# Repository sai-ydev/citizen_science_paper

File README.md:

# Purple Daisy RP2350A STEAM Platform #

This is the repository for the Purple Daisy Platform based on the [Raspberry Pi RP2350A Microcontroller](https://www.raspberrypi.com/products/rp2350/). This is an open-source platform to conduct citizen science experiments using the Raspberry Pi RP2350A microcontroller. 

The board looks something like shown in the image below:

The components of the board are highlighted in the image below. They are as follows:

1. Raspberry PI RP2350A microcontroller
2. RGB seven segment display - 4 characters
3. MicroSD card slot
4. Buzzer
5. WiFi Module
6. USB-C port
7. Soil Moisture sensor
8. AS3935 Lightning Sensor
9. pH Sensor + Conditioning Circuit
10. Liquid Temperature sensor
11. QwiiC I2C Sensor port to connect additional sensors
12. Real Time Clock for Calendar Keeping
13. Debug Port for debugging
14. BME690 Air Quality Sensor
15. ENS210 Temperature Humidity Sensor

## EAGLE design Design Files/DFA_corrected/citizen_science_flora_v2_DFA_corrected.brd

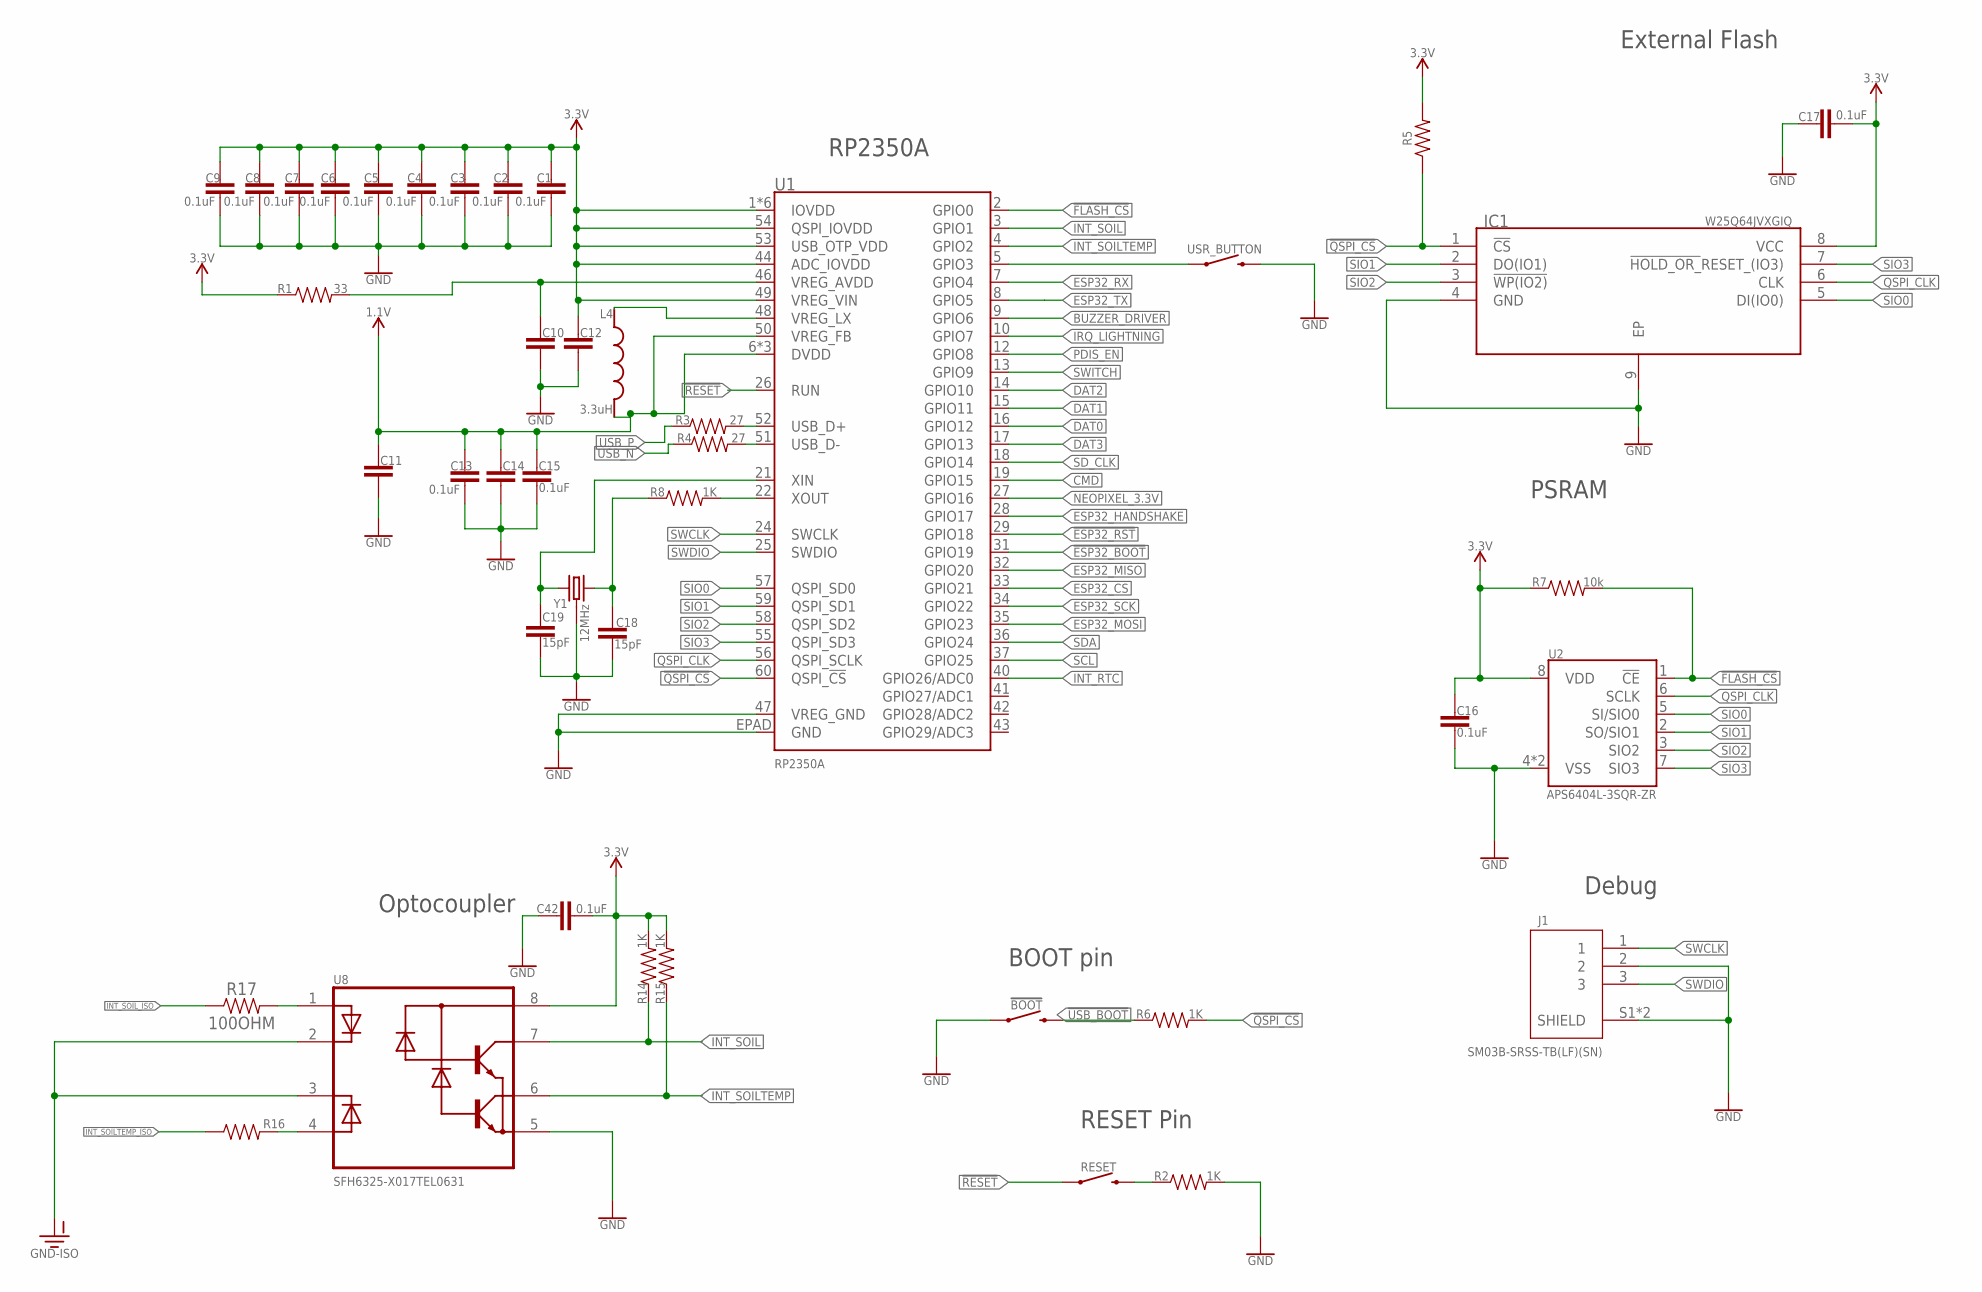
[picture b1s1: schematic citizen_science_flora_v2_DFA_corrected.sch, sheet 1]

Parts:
!BOOT: MOMENTARY-SWITCH-SPST-SMD-4.6X2.8MM; TACTILE_SWITCH_SMD_4.6X2.8MM
C1, C2, C3, C4, C5, C6, C7, C8, C9, C13, C15, C16, C17, C42: 0.1uF; 0402
C10, C11, C12, C14: 4.7UF0402; 0402
C18, C19: 15pF; 0402
IC1: W25Q64JVXGIQ; SON80P400X400X50-9N
J1: SM03B-SRSS-TB(LF)(SN); JST_SM03B-SRSS-TB(LF)(SN)
L4: 3.3uH; IND_LQH2MCN120K02L
R1: 33; 0402
R2, R6, R8, R14, R15: 1K; 0402
R3, R4: 27; 0402
R5: 0402
R7: 10k; 0402
R16, R17: 100OHM; 0402
RESET: MOMENTARY-SWITCH-SPST-SMD-4.6X2.8MM; TACTILE_SWITCH_SMD_4.6X2.8MM
U1: RP2350A
U2: APS6404L-3SQR-ZR
U8: SFH6325-X017TEL0631; SOIC127P599X175-8N
USR_BUTTON: MOMENTARY-SWITCH-SPST-SMD-4.6X2.8MM; TACTILE_SWITCH_SMD_4.6X2.8MM
Y1: 12MHz; CRYSTAL-SMD-3.2X2.5MM

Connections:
1.1V: C11.1, C13.1, C14.1, C15.1, L4.2, U1.6 (DVDD), U1.23 (DVDD), U1.39 (DVDD), U1.50 (VREG_FB)
3.3V: C1.1, C2.1, C3.1, C4.1, C5.1, C6.1, C7.1, C8.1, C9.1, C12.1, C16.1, C17.2, C42.2, IC1.8 (VCC), R1.1, R5.2, R7.1, R14.2, R15.2, U1.1 (IOVDD), U1.11 (IOVDD), U1.20 (IOVDD), U1.30 (IOVDD), U1.38 (IOVDD), U1.44 (ADC_IOVDD), U1.45 (IOVDD), U1.49 (VREG_VIN), U1.53 (USB_OTP_VDD), U1.54 (QSPI_IOVDD), U2.8 (VDD), U8.8 (C(VCC)); also elsewhere on the board
!ESP32_BOOT: U1.31 (GPIO19); also elsewhere on the board
!ESP32_RST: U1.29 (GPIO18); also elsewhere on the board
!FLASH_CS: R7.2, U1.2 (GPIO0), U2.1 (!CE!)
!QSPI_CS: IC1.1 (!CS), R5.1, R6.2, U1.60 (QSPI_!CS!)
!RESET: RESET.1, RESET.2 (1), U1.26 (RUN)
!USB_BOOT: !BOOT.3 (2), !BOOT.4 (2), R6.1
BUZZER_DRIVER: U1.9 (GPIO6); also elsewhere on the board
CMD: U1.19 (GPIO15); also elsewhere on the board
DAT0: U1.16 (GPIO12); also elsewhere on the board
DAT1: U1.15 (GPIO11); also elsewhere on the board
DAT2: U1.14 (GPIO10); also elsewhere on the board
DAT3: U1.17 (GPIO13); also elsewhere on the board
ESP32_CS: U1.33 (GPIO21); also elsewhere on the board
ESP32_HANDSHAKE: U1.28 (GPIO17); also elsewhere on the board
ESP32_MISO: U1.32 (GPIO20); also elsewhere on the board
ESP32_MOSI: U1.35 (GPIO23); also elsewhere on the board
ESP32_RX: U1.7 (GPIO4); also elsewhere on the board
ESP32_SCK: U1.34 (GPIO22); also elsewhere on the board
ESP32_TX: U1.8 (GPIO5); also elsewhere on the board
GND: !BOOT.1, !BOOT.2 (1), C1.2, C2.2, C3.2, C4.2, C5.2, C6.2, C7.2, C8.2, C9.2, C10.2, C11.2, C12.2, C13.2, C14.2, C15.2, C16.2, C17.1, C18.2, C19.2, C42.1, IC1.4 (GND), IC1.9 (EP), J1.2, J1.S1 (SHIELD), J1.S2 (SHIELD), R2.2, U1.47 (VREG_GND), U1.EPAD (GND), U2.4 (VSS), U2.9 (VSS), U8.5 (E(GND)), USR_BUTTON.3 (2), USR_BUTTON.4 (2), Y1.2 (GND), Y1.4 (GND); also elsewhere on the board
GND-ISO: U8.2 (C1), U8.3 (C2); also elsewhere on the board
INT_RTC: U1.40 (GPIO26/ADC0); also elsewhere on the board
INT_SOIL: R14.1, U1.3 (GPIO1), U8.7 (C1(VO1))
INT_SOILTEMP: R15.1, U1.4 (GPIO2), U8.6 (C2(VO2))
INT_SOILTEMP_ISO: R16.1; also elsewhere on the board
INT_SOIL_ISO: R17.1; also elsewhere on the board
IRQ_LIGHTNING: U1.10 (GPIO7); also elsewhere on the board
unnamed: C10.1, R1.2, U1.46 (VREG_AVDD)
unnamed: L4.1, U1.48 (VREG_LX)
unnamed: R2.1, RESET.3 (2), RESET.4 (2)
unnamed: C18.1, R8.1, Y1.3 (2)
unnamed: C19.1, U1.21 (XIN), Y1.1
unnamed: R8.2, U1.22 (XOUT)
unnamed: R16.2, U8.4 (A2)
unnamed: R17.2, U8.1 (A1)
unnamed: U1.5 (GPIO3), USR_BUTTON.1, USR_BUTTON.2 (1)
NEOPIXEL_3.3V: U1.27 (GPIO16); also elsewhere on the board
PDIS_EN: U1.12 (GPIO8); also elsewhere on the board
QSPI_CLK: IC1.6 (CLK), U1.56 (QSPI_SCLK), U2.6 (SCLK)
SCL: U1.37 (GPIO25); also elsewhere on the board
SDA: U1.36 (GPIO24); also elsewhere on the board
SD_CLK: U1.18 (GPIO14); also elsewhere on the board
SIO0: IC1.5 (DI(IO0)), U1.57 (QSPI_SD0), U2.5 (SI/SIO0)
SIO1: IC1.2 (DO(IO1)), U1.59 (QSPI_SD1), U2.2 (SO/SIO1)
SIO2: IC1.3 (!WP(IO2)), U1.58 (QSPI_SD2), U2.3 (SIO2)
SIO3: IC1.7 (!HOLD_OR_!RESET_(IO3)), U1.55 (QSPI_SD3), U2.7 (SIO3)
SWCLK: J1.1, U1.24 (SWCLK)
SWDIO: J1.3, U1.25 (SWDIO)
SWITCH: U1.13 (GPIO9); also elsewhere on the board
USBD_N: R4.2, U1.51 (USB_D-)
USBD_P: R3.2, U1.52 (USB_D+)
USB_N: R4.1; also elsewhere on the board
USB_P: R3.1; also elsewhere on the board

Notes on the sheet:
RP2350A
RESET Pin
External Flash
BOOT pin
PSRAM
Debug
Optocoupler

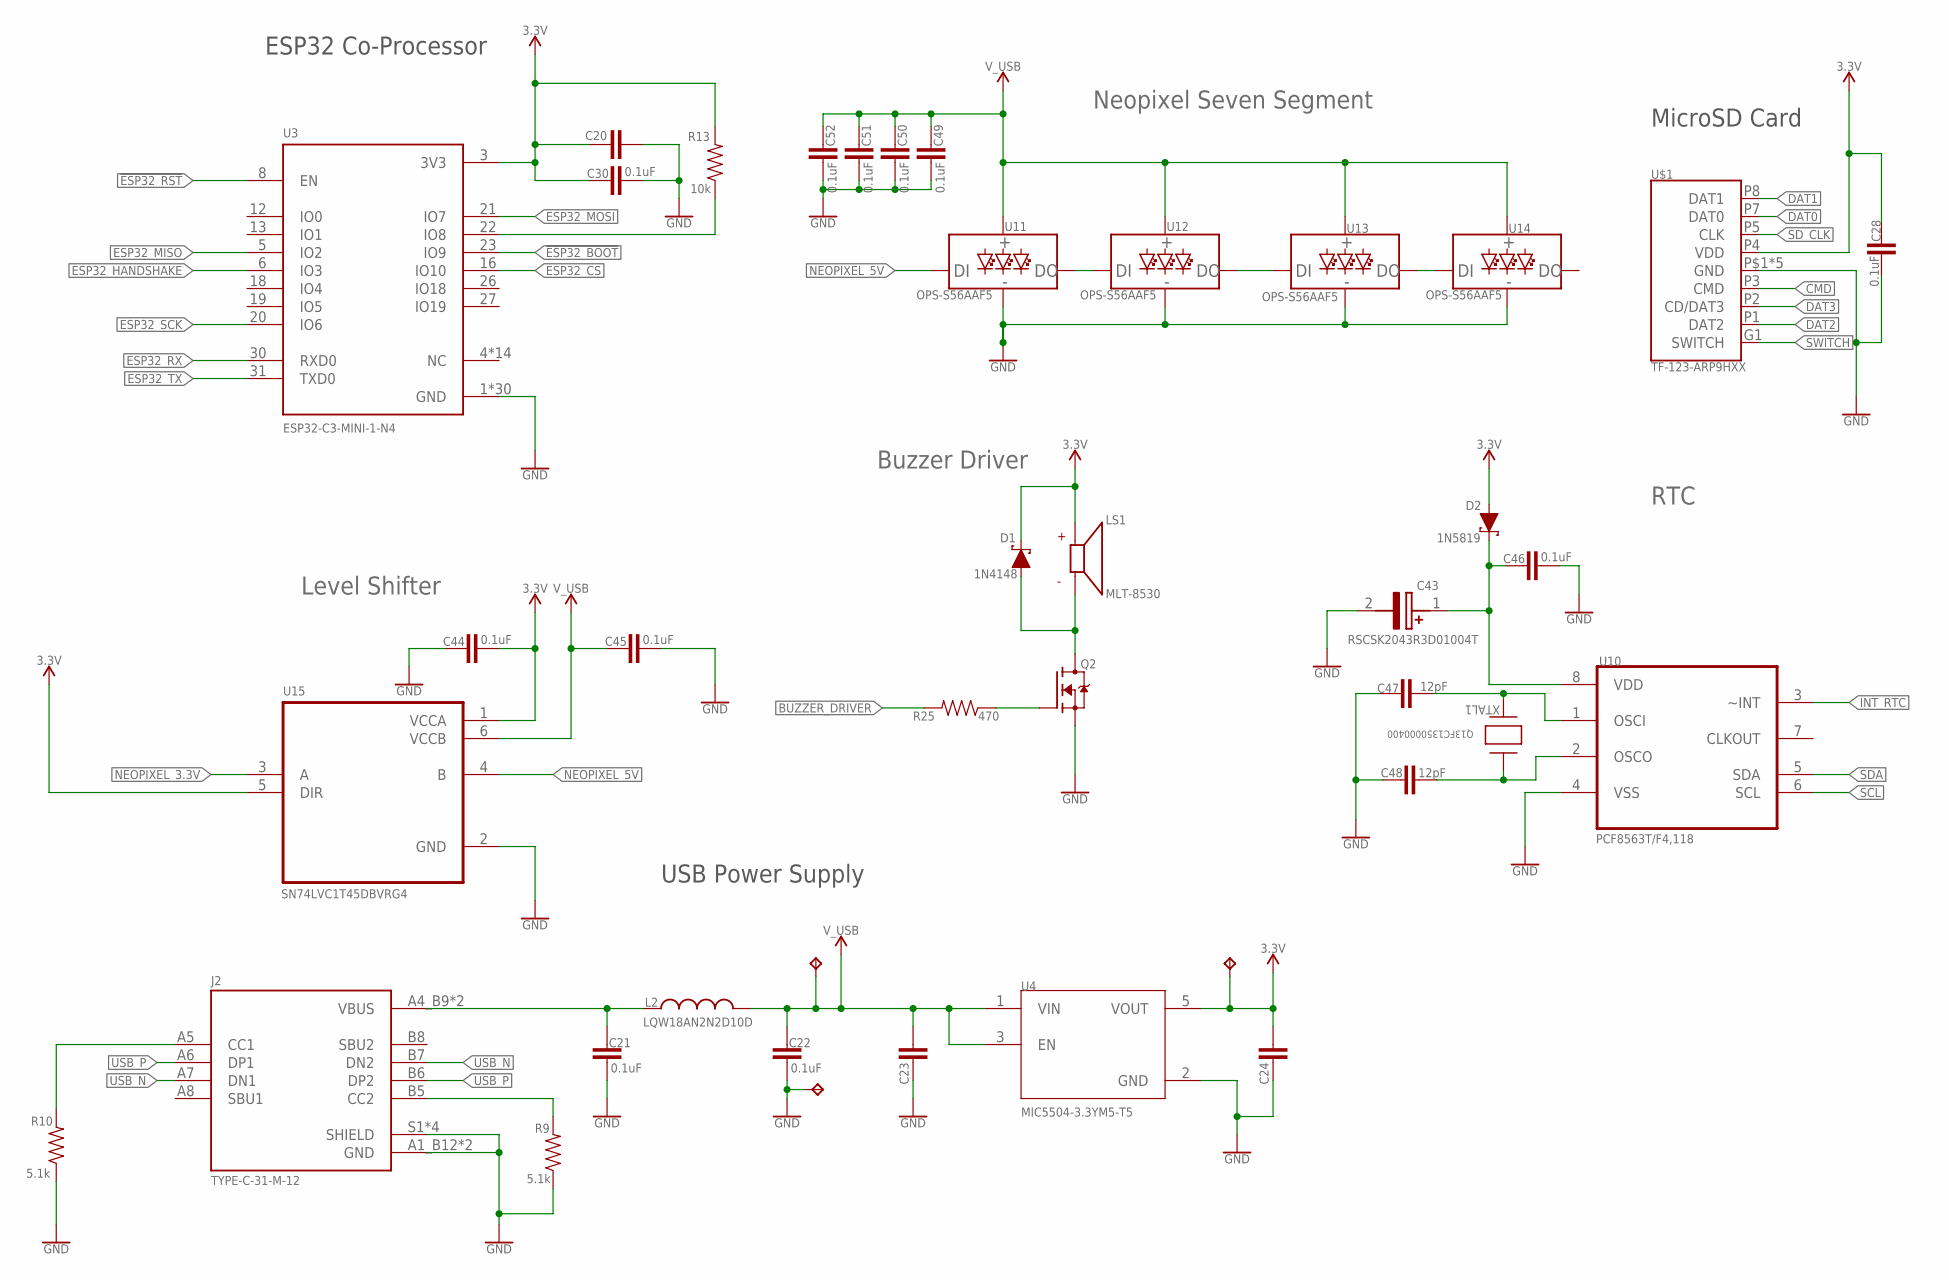
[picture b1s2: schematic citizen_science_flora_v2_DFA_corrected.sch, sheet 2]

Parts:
3.3V: TPB1,27; B1,27
C20, C23, C24: 10UF0402; 0402
C21, C22, C28, C30, C44, C45, C46, C49, C50, C51, C52: 0.1uF; 0402
C43: RSCSK2043R3D01004T
C47, C48: 12pF; 0402
D1: 1N4148; SOD-323
D2: 1N5819; SOD-323
GND: TPB1,27; B1,27
J2: TYPE-C-31-M-12; HRO_TYPE-C-31-M-12
L2: LQW18AN2N2D10D; INDC1608X100N
LS1: MLT-8530; XDCR_CMT-8504-100-SMT-TR
Q2: BSS138; SOT95P240X111-3N
R9, R10: 5.1k; 0402
R13: 10k; 0402
R25: 470; 0402
U3: ESP32-C3-MINI-1-N4; XCVR_ESP32-C3-MINI-1-N4
U4: MIC5504-3.3YM5-T5; SOT95P280X145-5N
U10: PCF8563T/F4,118; SOIC127P600X175-8N
U11, U12, U13, U14: OPS-S56AAF5
U15: SN74LVC1T45DBVRG4; SOT95P280X145-6N
U$1: TF-123-ARP9HXX; MICROSDCARD
USB: V_USB; B1,27
XTAL1: Q13FC1350000400; XTAL_FC-135_EPS

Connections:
3.3V: 3.3V.TP, C20.1, C24.2, C28.1, C30.1, C44.2, D1.C, D2.A, LS1.P, R13.2, U3.3 (3V3), U4.5 (VOUT), U15.1 (VCCA), U15.5 (DIR), U$1.P4 (VDD); also elsewhere on the board
!ESP32_BOOT: U3.23 (IO9); also elsewhere on the board
!ESP32_RST: U3.8 (EN); also elsewhere on the board
BUZZER_DRIVER: R25.2; also elsewhere on the board
CMD: U$1.P3 (CMD); also elsewhere on the board
DAT0: U$1.P7 (DAT0); also elsewhere on the board
DAT1: U$1.P8 (DAT1); also elsewhere on the board
DAT2: U$1.P1 (DAT2); also elsewhere on the board
DAT3: U$1.P2 (CD/DAT3); also elsewhere on the board
ESP32_CS: U3.16 (IO10); also elsewhere on the board
ESP32_HANDSHAKE: U3.6 (IO3); also elsewhere on the board
ESP32_MISO: U3.5 (IO2); also elsewhere on the board
ESP32_MOSI: U3.21 (IO7); also elsewhere on the board
ESP32_RX: U3.30 (RXD0); also elsewhere on the board
ESP32_SCK: U3.20 (IO6); also elsewhere on the board
ESP32_TX: U3.31 (TXD0); also elsewhere on the board
GND: C20.2, C21.2, C22.2, C23.1, C24.1, C28.2, C30.2, C43.2 (-), C44.1, C45.2, C46.2, C47.1, C48.1, C49.2, C50.2, C51.2, C52.2, GND.TP, J2.A1_B12 (GND), J2.B1_A12 (GND), J2.S1 (SHIELD), J2.S2 (SHIELD), J2.S3 (SHIELD), J2.S4 (SHIELD), Q2.2 (S), R9.1, R10.1, U3.1 (GND), U3.2 (GND), U3.11 (GND), U3.14 (GND), U3.36 (GND), U3.37 (GND), U3.38 (GND), U3.39 (GND), U3.40 (GND), U3.41 (GND), U3.42 (GND), U3.43 (GND), U3.44 (GND), U3.45 (GND), U3.46 (GND), U3.47 (GND), U3.48 (GND), U3.49_1 (GND), U3.49_2 (GND), U3.49_3 (GND), U3.49_4 (GND), U3.49_5 (GND), U3.49_6 (GND), U3.49_7 (GND), U3.49_8 (GND), U3.49_9 (GND), U3.50 (GND), U3.51 (GND), U3.52 (GND), U3.53 (GND), U4.2 (GND), U10.4 (VSS), U11.P$3 (GND), U12.P$3 (GND), U13.P$3 (GND), U14.P$3 (GND), U15.2 (GND), U$1.P6 (GND), U$1.P$1 (GND), U$1.P$2 (GND), U$1.P$3 (GND), U$1.P$4 (GND); also elsewhere on the board
INT_RTC: U10.3 (~INT); also elsewhere on the board
unnamed: J2.A5 (CC1), R10.2
unnamed: J2.B5 (CC2), R9.2
unnamed: C21.1, J2.A4_B9 (VBUS), J2.B4_A9 (VBUS), L2.1
unnamed: R13.1, U3.22 (IO8)
unnamed: U11.P$2 (DO), U12.P$4 (DI)
unnamed: U12.P$2 (DO), U13.P$4 (DI)
unnamed: U13.P$2 (DO), U14.P$4 (DI)
unnamed: D1.A, LS1.N, Q2.3 (D)
unnamed: Q2.1 (G), R25.1
unnamed: C43.1 (+), C46.1, D2.C, U10.8 (VDD)
unnamed: C48.2, U10.2 (OSCO), XTAL1.1
unnamed: C47.2, U10.1 (OSCI), XTAL1.2
NEOPIXEL_3.3V: U15.3 (A); also elsewhere on the board
NEOPIXEL_5V: U11.P$4 (DI), U15.4 (B)
SCL: U10.6 (SCL); also elsewhere on the board
SDA: U10.5 (SDA); also elsewhere on the board
SD_CLK: U$1.P5 (CLK); also elsewhere on the board
SWITCH: U$1.G1 (SWITCH); also elsewhere on the board
USB_N: J2.A7 (DN1), J2.B7 (DN2); also elsewhere on the board
USB_P: J2.A6 (DP1), J2.B6 (DP2); also elsewhere on the board
V_USB: C22.1, C23.2, C45.1, C49.1, C50.1, C51.1, C52.1, L2.2, U4.1 (VIN), U4.3 (EN), U11.P$1 (VCC), U12.P$1 (VCC), U13.P$1 (VCC), U14.P$1 (VCC), U15.6 (VCCB), USB.TP; also elsewhere on the board

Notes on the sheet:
MicroSD Card
ESP32 Co-Processor
USB Power Supply
Neopixel Seven Segment
Level Shifter
Buzzer Driver
RTC

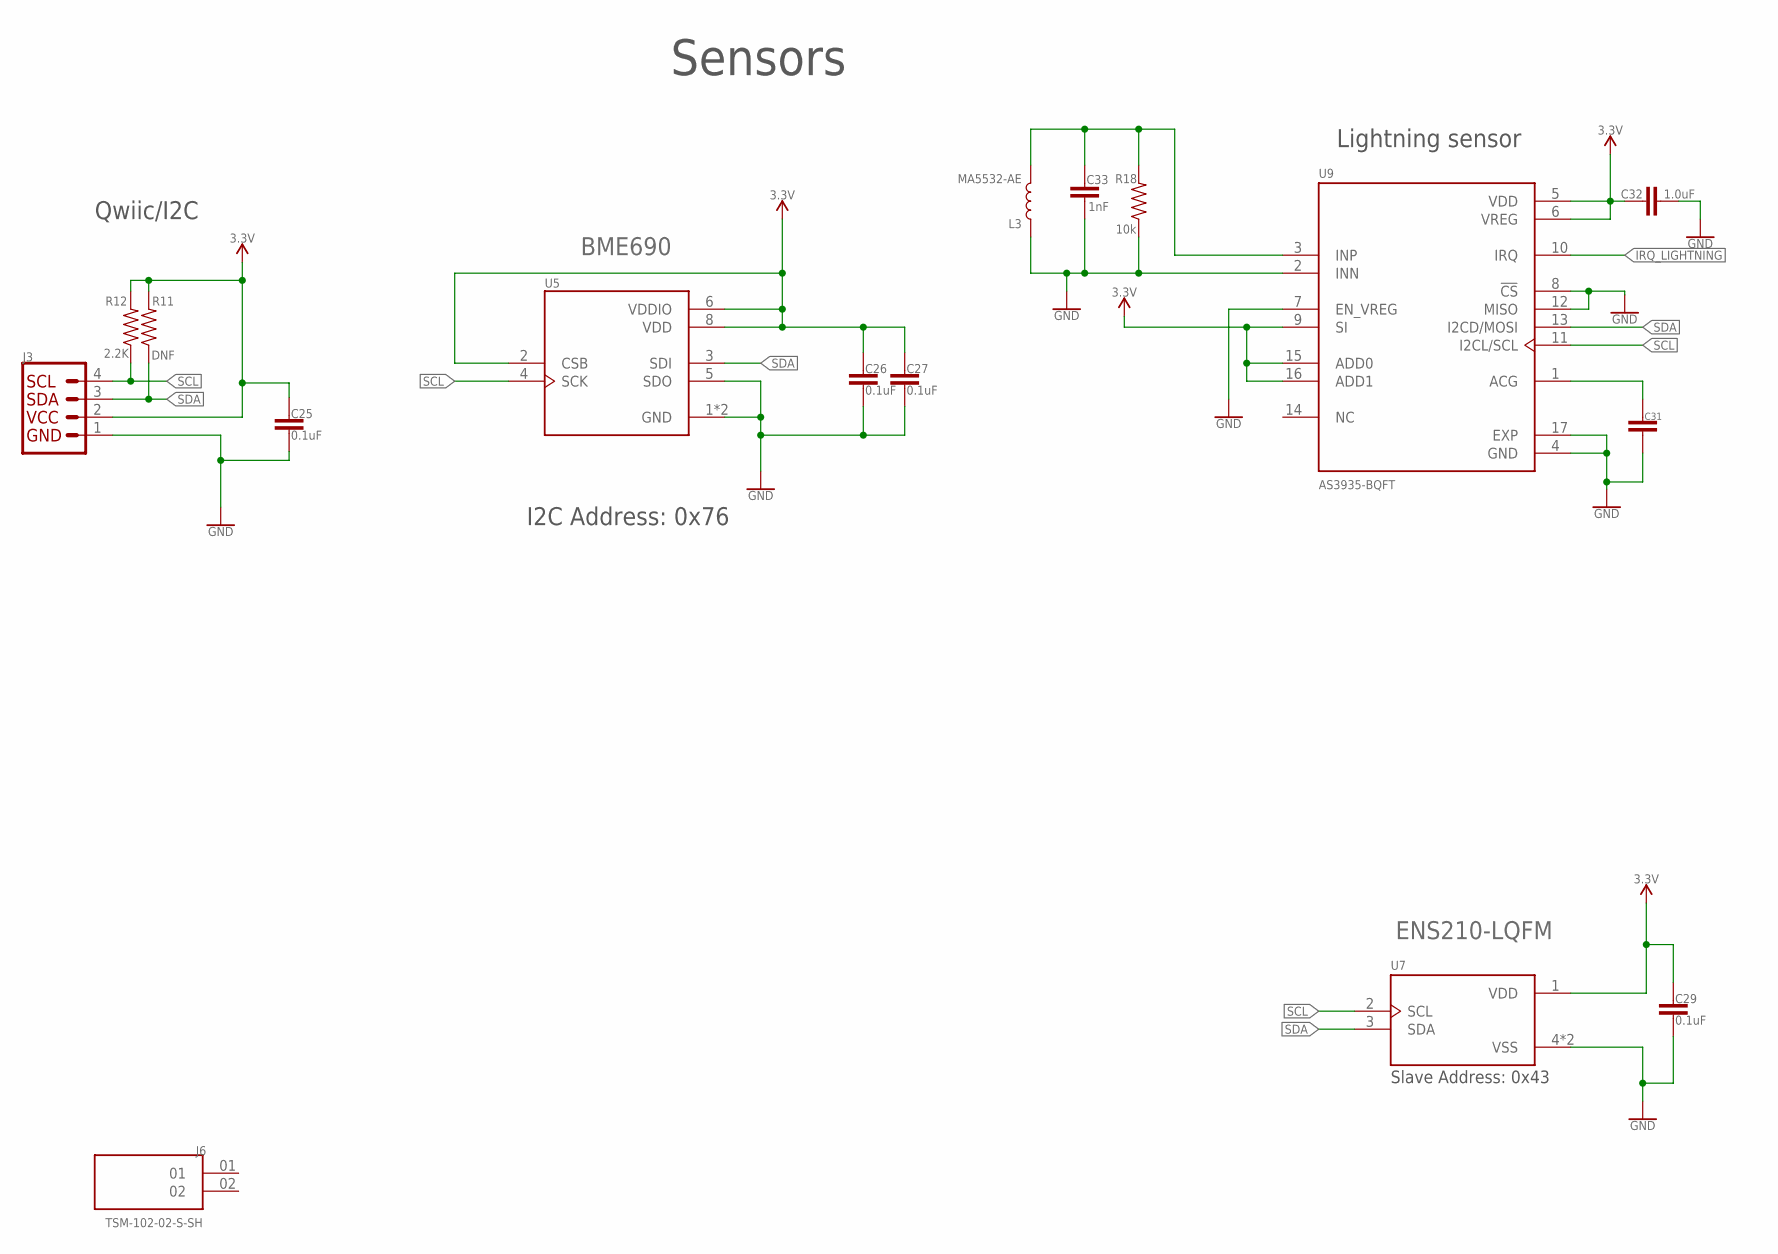
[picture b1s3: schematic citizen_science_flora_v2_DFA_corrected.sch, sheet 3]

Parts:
C25, C26, C27, C29: 0.1uF; 0402
C31: 10UF0402; 0402
C32: 1.0uF; 0402
C33: 1nF; 0402
J3: QWIIC_CONNECTORJS-1MM; 1X04_1MM_RA
J6: TSM-102-02-S-SH; SAMTEC_TSM-102-02-S-SH
L3: MA5532-AE
R11: DNF; 0402
R12: 2.2K; 0402
R18: 10k; 0402
U5: BME690; IC_BME688
U7: ENS210-LQFM; XDCR_ENS210-LQFM
U9: AS3935-BQFT; QFN65P400X400X80-17N

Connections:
3.3V: C25.1, C26.1, C27.1, C29.1, C32.1, J3.2, R11.2, R12.2, U5.2 (CSB), U5.6 (VDDIO), U5.8 (VDD), U7.1 (VDD), U9.5 (VDD), U9.6 (VREG), U9.9 (SI), U9.15 (ADD0), U9.16 (ADD1); also elsewhere on the board
GND: C25.2, C26.2, C27.2, C29.2, C31.2, C32.2, C33.2, J3.1, L3.1, R18.1, U5.1 (GND), U5.5 (SDO), U5.7 (GND), U7.4 (VSS), U7.5 (VSS), U9.2 (INN), U9.4 (GND), U9.7 (EN_VREG), U9.8 (!CS), U9.12 (MISO), U9.17 (EXP); also elsewhere on the board
IRQ_LIGHTNING: U9.10 (IRQ); also elsewhere on the board
unnamed: C31.1, U9.1 (ACG)
unnamed: C33.1, L3.2, R18.2, U9.3 (INP)
SCL: J3.4, R12.1, U5.4 (SCK), U7.2 (SCL), U9.11 (I2CL/SCL); also elsewhere on the board
SDA: J3.3, R11.1, U5.3 (SDI), U7.3 (SDA), U9.13 (I2CD/MOSI); also elsewhere on the board

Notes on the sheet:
Sensors
Qwiic/I2C
Slave Address: 0x43
Lightning sensor
I2C Address: 0x76

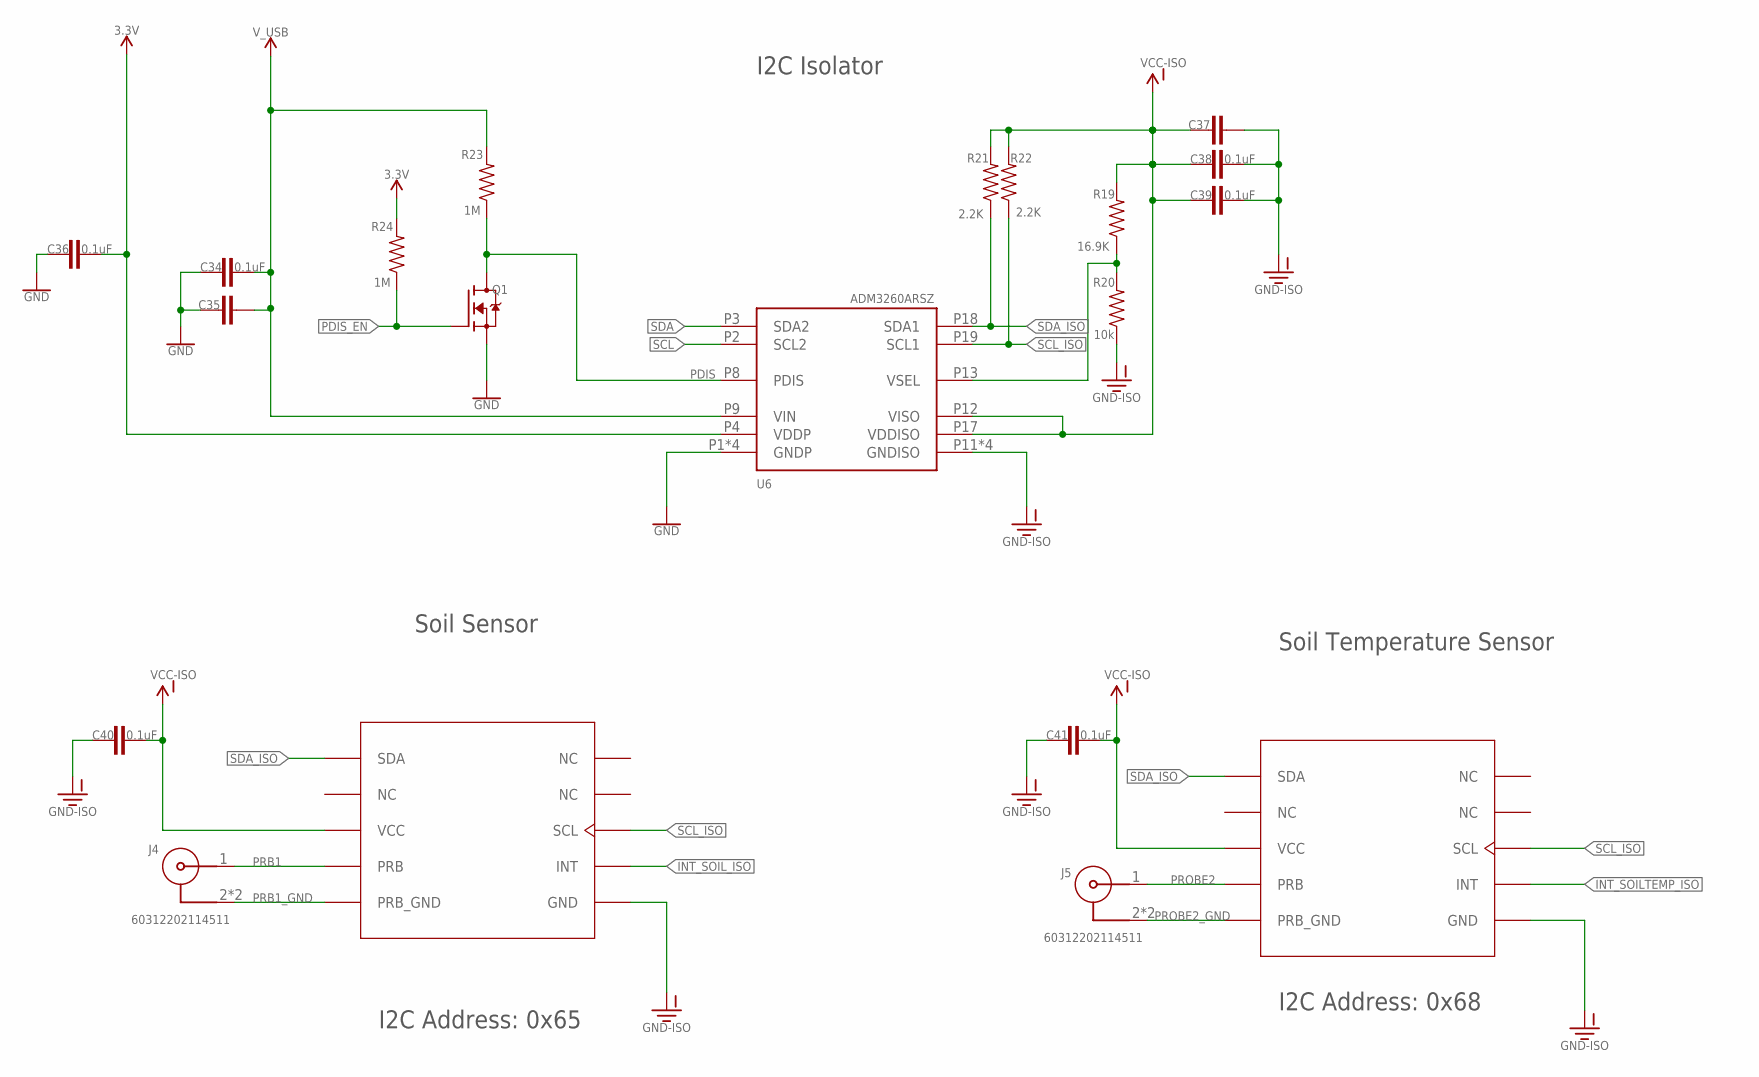
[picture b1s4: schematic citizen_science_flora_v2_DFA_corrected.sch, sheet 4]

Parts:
C34, C36, C38, C39, C40, C41: 0.1uF; 0402
C35, C37: 10UF0402; 0402
J4, J5: 60312202114511
Q1: BSS138; SOT95P240X111-3N
R19: 16.9K; 0402
R20: 10k; 0402
R21, R22: 2.2K; 0402
R23, R24: 1M; 0402
U6: ADM3260ARSZ; SSOP20
U$2, U$3: PH-OEM; PH_SENSOR

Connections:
3.3V: C36.2, R24.2, U6.P4 (VDDP); also elsewhere on the board
GND: C34.1, C35.1, C36.1, Q1.2 (S), U6.P1 (GNDP), U6.P5 (GNDP), U6.P7 (GNDP), U6.P10 (GNDP); also elsewhere on the board
GND-ISO: C37.2, C38.2, C39.2, C40.1, C41.1, R20.1, U6.P11 (GNDISO), U6.P14 (GNDISO), U6.P16 (GNDISO), U6.P20 (GNDISO), U$2.P$6 (GND), U$3.P$6 (GND); also elsewhere on the board
INT_SOILTEMP_ISO: U$3.P$7 (INT); also elsewhere on the board
INT_SOIL_ISO: U$2.P$7 (INT); also elsewhere on the board
unnamed: R19.1, R20.2, U6.P13 (VSEL)
PDIS: Q1.3 (D), R23.1, U6.P8 (PDIS)
PDIS_EN: Q1.1 (G), R24.1; also elsewhere on the board
PRB1: J4.1, U$2.P$4 (PRB)
PRB1_GND: J4.2, J4.3 (2), U$2.P$5 (PRB_GND)
PROBE2: J5.1, U$3.P$4 (PRB)
PROBE2_GND: J5.2, J5.3 (2), U$3.P$5 (PRB_GND)
SCL: U6.P2 (SCL2); also elsewhere on the board
SCL_ISO: R22.1, U6.P19 (SCL1), U$2.P$8 (SCL), U$3.P$8 (SCL)
SDA: U6.P3 (SDA2); also elsewhere on the board
SDA_ISO: R21.1, U6.P18 (SDA1), U$2.P$1 (SDA), U$3.P$1 (SDA)
VCC-ISO: C37.1, C38.1, C39.1, C40.2, C41.2, R19.2, R21.2, R22.2, U6.P12 (VISO), U6.P17 (VDDISO), U$2.P$3 (VCC), U$3.P$3 (VCC)
V_USB: C34.2, C35.2, R23.2, U6.P9 (VIN); also elsewhere on the board

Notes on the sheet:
I2C Isolator
Soil Sensor
Soil Temperature Sensor
I2C Address: 0x68
I2C Address: 0x65

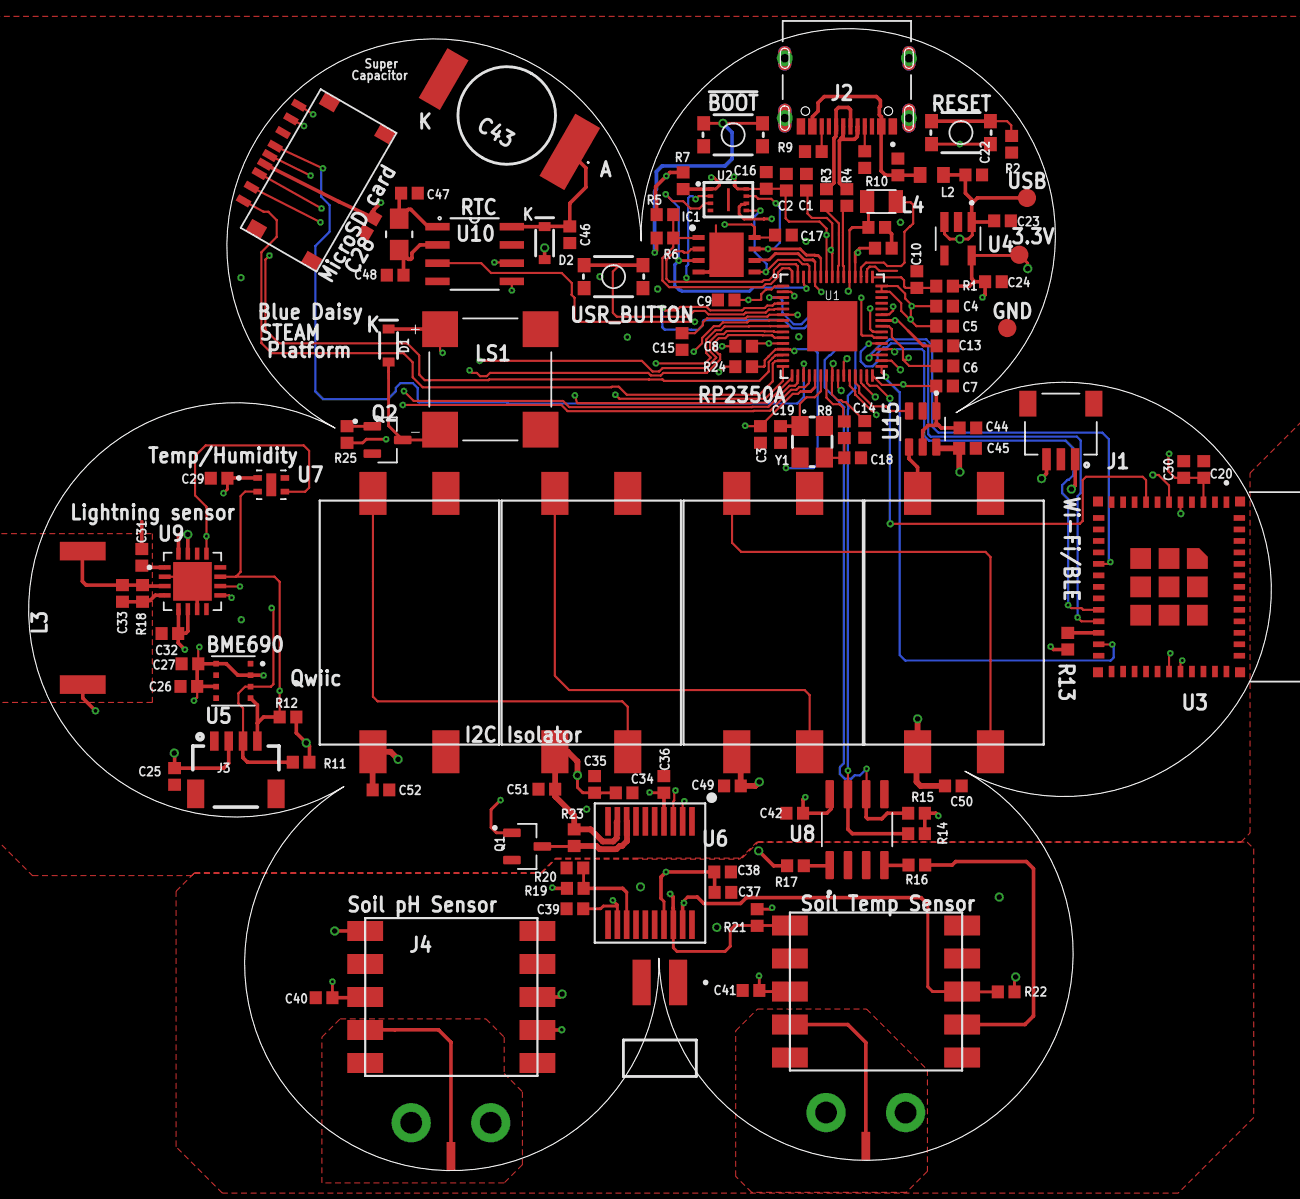
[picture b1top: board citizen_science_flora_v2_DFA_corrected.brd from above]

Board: 4 copper layers, 86.6 x 79.6 mm, 118 parts (0 on the bottom side), 80 nets.

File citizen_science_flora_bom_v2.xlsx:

Comment | Designator | *Manufacturer Part Number | *Quantity | Manufacturer(Optional) | Package(Optional)
SM04B-SRSS-TB(LF)(SN) | J3 | SM04B-SRSS-TB(LF)(SN) | 1 | JST | SMD,P=1mm,Surface Mount，Right Angle
0.1uF | C1,C2,C3,C4,C5,C6,C7,C8,C9,C13,C15,C16,C17,C21,C22,C25,C26,C27,C28,C29,C30,C34,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 | 0402B104K250NT | 35 | FH | 0402
1.0uF | C32 | CL05A105KP5NNNC | 1 | Samsung | 0402
1K | R2,R6,R8,R14,R15 | 0402WGF1001TCE | 5 | Uni-Royal | 0402
1M | R23,R24 | 0402WGF1004TCE | 2 | Uni-Royal | 0402
1N5819 | D1,D2 | 1SS404 | 2 | Jiangsu Changjing | SOD-323
1nF | C33 | 0402B102K500NT | 1 | FH | 0402
2.2K | R12,R21,R22 | 0402WGF2201TCE | 3 | Uni-Royal | 0402
3.3µH | L1 | SDFL2012Q3R3KTF | 1 | Sunlord | 0805
4.7uF | C10,C11,C12,C14 | CL05A475MP5NRNC | 4 | Samsung | 0402
5.1k | R9,R10 | 0402WGF5101TCE | 2 | Uni-Royal | 0402
10K | R18,R20,R7,R13 | 0402WGJ0103TCE | 4 | Uni-Royal | 0402
10uF | C20,C23,C24,C31,C35,C37 | CL05A106MQ5NUNC | 6 | Samsung | 0402
12MHz | Y1 | 7B012000R01 | 1 | HD | SMD3225-4P
12pF | C47,C48 | 0402CG120J500NT | 2 | FH | 0402
15pF | C18,C19 | 0402CG150J500NT | 2 | FH | 0402
16.9K | R19 | 0402WGF1692TCE | 1 | Uni-Royal | 0402
27 | R3,R4 | SCR0603J27R | 2 | VO | 0402
33 | R1 | 0402WGF330JTCE | 1 | Uni-Royal | 0402
100 | R16,R17 | 0402WGF1000TCE | 2 | Uni-Royal | 0402
BSS138 | Q1,Q2 | Si2308BDS-T1-GE3 | 2 | Vishay | SOT-23-3
470 | R25 | RMS04FT4700 | 1 | TA-I Tech | 0402
ADM3260ARSZ | U6 | ADM3260ARSZ | 1 | Analog Devices | SSOP-20
APS6404L-3SQR-ZR | U2 | APS6404L-3SQR-ZR | 1 | Ap Memory | USON8
AS3935-BQFT | U9 | AS3935-BQFT | 1 | Sciosense | 16LD MLPQ
BME690 | U5 | BME690 | 1 | Bosch | LGA-8_3x3mm
ENS210-LQFM | U7 | ENS210-LQFM | 1 | Sciosense | QFN4_2x2mm
ESP32-C3-MINI-1-N4 | U3 | ESP32-C3-MINI-1-N4 | 1 | Espressif | ESP32-C3-MINI-1-N4
LQW18AN2N2D10D | L2 | LQW18AN2N2C80D | 1 | Murata | 0603
MA5532-AE | L3 | MA5532-AE | 1 | Coil craft | SMD
MIC5504-3.3YM5-T5 | U4 | TPMIC5504-3.3YM5 | 1 | Tech Public | SOT-23-5
MLT-8530 | LS1 | MLT-8530 | 1 | Jiangsu Huaneng Elec | SMD
MOMENTARY-SWITCH-SPST-SMD-4.6X2.8MM | !BOOT,RESET,USR_BUTTON | KMR221GLFS | 3 | C&K | SMD
PCF8563T/F4 118 | U10 | PCF8563T/F4 118 | 1 | NXP | SOIC-8
Q13FC1350000400 | XTAL1 | Q13FC13500002 | 1 | Seiko Epson | SMD3215-2P
RP2350A | U1 | RP2350A | 1 | Raspberry Pi | QFN-60
RSCSK2043R3D01004T | C43 | RSCSK2043R3D01004T | 1 | Elna America | SMD
SFH6325-X017TEL0631 | U8 | EL0631(TA) | 1 | Everlight Electronics | SOP-8
SM03B-SRSS-TB(LF)(SN) | J1 | SM03B-SRSS-TB(LF)(SN) | 1 | JST | SMD,P=1mm,Surface Mount，Right Angle
SN74LVC1T45DBVRG4 | U15 | SN74LVC1T45DBVRG4 | 1 | Texas Instruments | SOT-23-6
TF-123-ARP9HXX | U$1 | TF-123-ARP9H17 | 1 | Xunpu | SMD
TYPE-C-31-M-12 | J2 | TYPE-C-31-M-12 | 1 | Korean Hroparts | SMD
W25Q64JVXGIQ | IC1 | W25Q64JVXGIQ | 1 | Winbond | XSON-8-EP(4x4)

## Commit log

2024-12-28 Daily check-in
2025-01-01 Added floral outline
2025-01-02 placed some components
2025-01-03 Add 3D packages to resistors
2025-01-05 Board file updates
2025-01-06 Updates to the design
2025-01-08 updates to brd files
2025-01-15 BoM file check-in
2025-02-08 Change to gerbers
2025-02-08 Updates to Gerber
2025-02-10 updated gerber files
2025-02-12 File re-org + DFA corrected version
2025-02-14 RP2040 design
2025-02-15 update to design files
2025-02-15 Board design files and BoM
2025-02-18 Updates to board design
2025-02-19 via and new gerber
    Added a new via and generated new gerbers
2025-03-27 pH Display firmware
2025-03-27 Image Check-in
2025-04-15 Checking in ENS210 drivers

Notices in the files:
parts and their libraries:
SparkFun-Switches: Licensing: Creative Commons ShareAlike 4.0 International - https://creativecommons.org/licenses/by-sa/4.0
